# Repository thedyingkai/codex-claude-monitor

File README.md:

# Codex / Claude 配额监视器

这套项目把 Codex 和 Claude Code CLI 的配额、重置时间与活动任务数汇总到一个只读 HTTPS API，并由 Keyes E32R28T（ESP32-32E + 2.8 英寸触摸屏）便携终端显示。

推荐直接在云服务器运行 `quota-monitor standalone`。一个进程同时负责额度采集、Hooks、SQLite 和 API，本地电脑无需再运行 Agent。Codex/Claude 的登录凭据仍由官方 CLI 保存在云服务器的当前用户目录，本项目不读取或复制 OAuth Token。

> v1 只服务同一位用户的一个 Codex 账号和一个 Claude 账号。它不提供网页后台，也不显示订阅到期日期。某个账号没有 5h 或 7d 窗口时，API 返回 `null`，终端显示 `N/A`。Standalone 只能统计云服务器上运行的 Codex/Claude 任务；本地电脑上的任务不会出现在计数中。

服务器内存要按 Go 服务和官方 CLI 的总占用估算。[Codex CLI 官方要求](https://github.com/openai/codex/blob/main/docs/install.md#system-requirements)至少 4GB、推荐 8GB，[Claude Code 官方要求](https://code.claude.com/docs/en/setup#system-requirements)4GB 以上，因此官方支持配置至少应有 4GB。Standalone 默认按 Codex → 释放 app-server → Claude 的顺序串行探测，减少两个 CLI 的内存重叠，但无法降低单个 CLI 的峰值。1 核、512MB 同时启用两者仍只适合无稳定保证的实验性试跑；至少应配置 1GB swap、保持默认串行模式并持续检查 OOM，现有业务出现内存压力时应关闭一个 provider 或升级内存。

## 交付内容

- `quota-monitor standalone`：推荐模式；在云服务器单进程运行 API、SQLite、额度采集和 Hooks，本地无需 Agent。
- `quota-monitor login codex|claude`：调用官方 CLI 完成交互登录；登录失效时重新执行即可，Standalone 会自动恢复采集。
- `quota-monitor server` + `quota-monitor agent`：兼容多机上报模式，适合确实需要统计多台电脑任务的场景。
- `quota-monitor hooks install/uninstall`：合并 Codex/Claude 用户配置、保留原 Hooks 和 Claude status line，并支持精确卸载。
- `quota-monitor token create/list/revoke`：在服务器本地管理 `agent:write` 和 `display:read` 令牌。
- `quota-monitor firmware publish`：在服务器本地校验并原子发布 E32R28T OTA 固件；公网没有上传接口。
- `deploy/`：Standalone 的用户级 systemd/Caddy 示例，以及兼容模式的 Docker Compose 部署。
- `firmware/`：PlatformIO + Arduino ESP32 + LVGL 固件；默认目标为 Keyes 62520093 E32R28T，旧 FireBeetle 目标仍可回归构建。
- `hardware/`：E32R28T 当前接线/BOM，以及已明确标记为停用的旧 DFRobot 载板和外壳资料。

```text
Codex app-server / Hooks ─┐
                          ├─> quota-monitor standalone + SQLite <──HTTPS── E32R28T
Claude /usage / Hooks ────┘             （云服务器）
```

Standalone 会直接把云端采集结果写入同一进程打开的 SQLite，不需要 `agent:write` 令牌。需要多机任务统计时仍可使用 Agent 模式：额度取 `observedAt` 最新的一份，不相加；任务按 `agentId + provider + sessionId` 去重。Agent 超过 45 秒未上报后不再计入在线或任务统计，任务事件 15 分钟没有更新则失效，额度样本超过 5 分钟标记为 `stale`。

## 开始使用

需要 Go 1.23 或更高版本。Windows、Linux amd64 和 Linux arm64 的构建方法见[快速开始](docs/quickstart.md)。云服务器推荐按以下顺序部署：

1. 在普通用户下安装官方 Codex/Claude CLI 和 `quota-monitor` 单文件程序。
2. 运行 `quota-monitor login codex`；需要 Claude 时再运行 `quota-monitor login claude`。
3. 安装 Hooks，并用 `systemd --user` 常驻运行 `quota-monitor standalone`。
4. 用宿主机 Caddy 把回环地址 `127.0.0.1:8787` 代理到 HTTPS 域名。
5. 把 Standalone 首次创建的 `display.token` 写入 ESP32。
6. 首次用 USB 烧录 v0.3.0；此后可从设备的临时 WPA2 配网页手动确认 OTA。

完整命令和服务文件见 [Standalone 云端部署](docs/standalone.md)。原来的 Docker server + 本地 Agent 流程仍保留在[快速开始](docs/quickstart.md)中，作为多机兼容方案。

生产环境必须使用受信任证书的 HTTPS。`allowInsecureHttp` 只用于回环地址上的本地开发；ESP32 固件不提供跳过证书校验的选项。

## 文档

- [快速开始与首次部署](docs/quickstart.md)
- [Standalone 单进程云端部署](docs/standalone.md)
- [运行维护、升级、备份与故障排查](docs/operations.md)
- [E32R28T 手机配网、熄屏与安全 OTA](docs/firmware-ota.md)
- [测试与验收清单](docs/testing.md)
- [R0.1 自动验证报告](docs/verification-report.md)
- [系统架构](docs/architecture.md)
- [安全说明](docs/security.md)
- [OpenAPI 3.1 契约](api/openapi.yaml)
- [E32R28T 购买、接线、烧录与装配](docs/hardware/README.md)

## API

公开路径固定为：

- `GET /healthz`：无需令牌，仅表示服务与数据库可用。
- `POST /api/v1/agent/report`：多机 Agent 兼容接口，需要与 `agentId` 绑定的 `agent:write` Bearer 令牌；Standalone 自身不经过此接口。
- `GET /api/v1/display/snapshot`：需要 `display:read` Bearer 令牌。
- `GET /api/v1/display/firmware/e32r28t/manifest`：需要同一只读令牌，返回当前发布版本、大小和 SHA-256。
- `GET /api/v1/display/firmware/e32r28t/{version}.bin`：需要同一只读令牌，流式下载当前发布固件。

服务不开放 CORS、管理页面、固件上传或远程令牌管理接口。设备配网页只存在于临时
WPA2 热点的 `192.168.4.1`，不会从正常 Wi-Fi 或云服务器开放。单次 Agent 上报上限为 64 KiB；
默认每个有效令牌每分钟最多 120 次请求，令牌校验前另有哈希指纹限速、全局上限
和并发上限。

## 安全与隐私

SQLite 只保存令牌 SHA-256 摘要、最新规范化额度、Agent 心跳和不透明任务 ID；不保存提示词、对话、路径、邮箱或 OAuth Token。Standalone 首次运行会创建一个只读显示令牌文件，必须像密码一样保护。多机模式的原始 Bearer 令牌只在创建时显示一次；应为每台设备单独签发，丢失设备后立即撤销。

仓库不应提交 `.env`、数据库、显示令牌、OAuth/API 凭据、Wi-Fi 配置、完整 Flash 备份、服务器私钥或现网专用 CA。`work/`、`dist/`、`.tools/` 和 `firmware/.pio/` 均为本地目录并已被 Git 忽略。编译固件前，将部署环境的公开设备根证书放到 `firmware/certs/device-root-ca.pem`；该文件只在本机使用，仓库仅提供不连接任何生产服务器的示例证书。

锂电池必须使用带保护板、极性匹配的 3.7V/1S 成品电池，禁止直接焊接软包电芯极耳。MX1.25-2P 只说明接口外形，插入 E32R28T 前仍必须按板上 `+/-` 丝印和万用表复核线序；充电温升、续航和外壳膨胀余量未经真机测量前不能视为量产验证完成。

## 许可证

[MIT](LICENSE)

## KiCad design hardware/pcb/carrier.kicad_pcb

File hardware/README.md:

# Hardware status

## Current build

Use [`e32r28t/`](e32r28t/) and [`wiring/`](wiring/). The selected Keyes
E32R28T is an integrated display/controller/charger board, so the current build
requires no custom PCB and no separate Wi-Fi module.

## Superseded files

The following directories are retained only as history from the abandoned
DFR0975 + DFR0665 carrier design:

- `pcb/`
- `rendered/pcb/`
- `enclosure/quota_display.scad` and its rendered outputs
- `scripts/` that generate or verify the old carrier

**Do not order, fabricate, assemble or print those files for E32R28T.** Their
production status is explicitly marked `SUPERSEDED — DO NOT ORDER OR FABRICATE`.
The current enclosure must be regenerated after measuring the purchased board,
battery, connector projection and required LiPo swelling clearance.

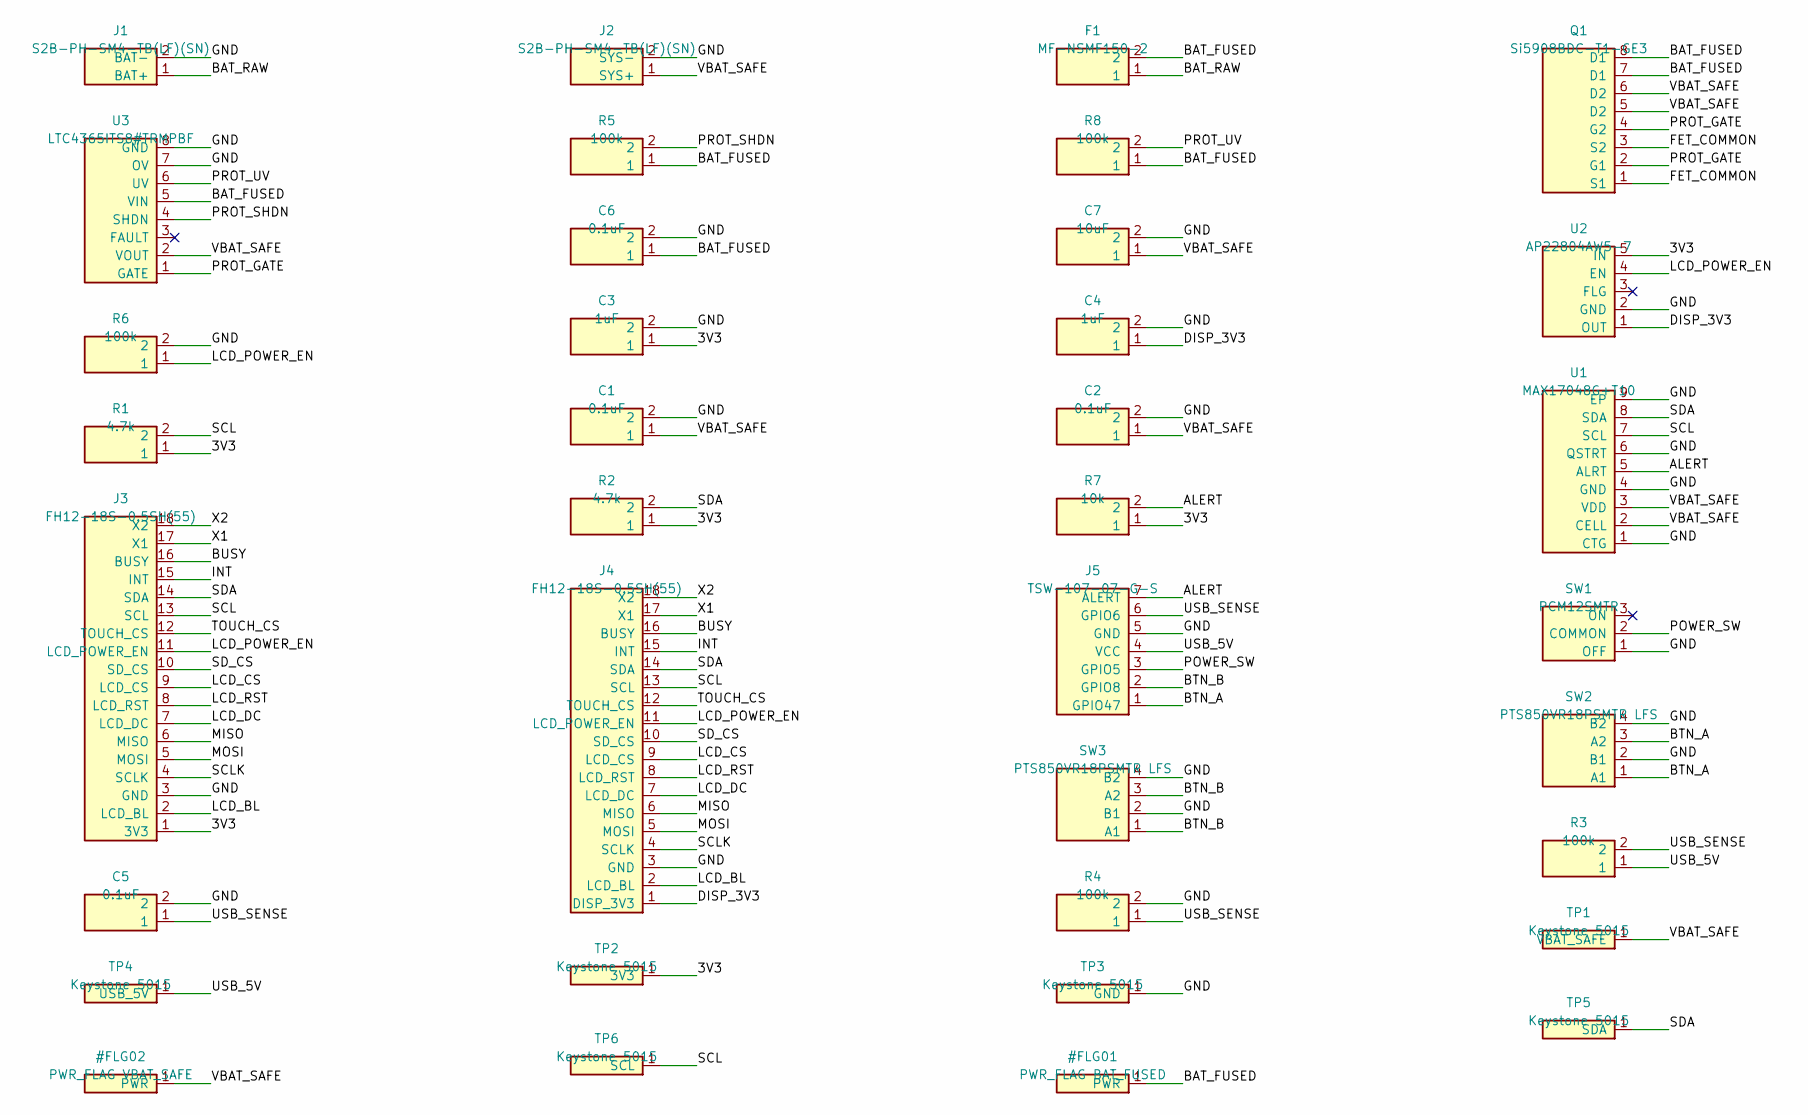
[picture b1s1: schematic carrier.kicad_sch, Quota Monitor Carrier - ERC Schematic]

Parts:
C1, C2, C5, C6: 0.1uF; C_0603
C3, C4: 1uF; C_0603
C7: 10uF; Murata_GRM21_Reflow_a1.10_b0.95_c0.95
F1: MF-NSMF150-2; Bourns_MF-NSMF_1206
J1, J2: S2B-PH-SM4-TB(LF)(SN); JST_PH_S2B-PH-SM4-TB_1x02_P2.00mm_Horizontal
J3, J4: FH12-18S-0.5SH(55); Hirose_FH12-18S-0.5SH_1x18_P0.50mm
J5: TSW-107-07-G-S; PinHeader_1x07_P2.54mm
Q1: Si5908BDC-T1-GE3; Vishay_1206-8_ChipFET
R1, R2: 4.7k; R_0603
R3, R4, R5, R6, R8: 100k; R_0603
R7: 10k; R_0603
SW1: PCM12SMTR; C&K_PCM12SMTR
SW2, SW3: PTS850VR18PSMTR LFS; C&K_PTS850_with_boss_actuator_plusX
TP1, TP2, TP3, TP4, TP5, TP6: Keystone 5015; Keystone_5015_SMT
U1: MAX17048G+T10; ADI_TDFN-8-1EP_2x2_P0.5_EP0.8x1.2
U2: AP22804AW5-7; Diodes_SOT-25_AP22804
U3: LTC4365ITS8#TRMPBF; TSOT-23-8

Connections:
3V3: C3.1, J3.1 (3V3), R1.1, R2.1, R7.1, TP2.1 (3V3), U2.5 (IN)
ALERT: J5.7 (ALERT), R7.2, U1.5 (ALRT)
BAT_FUSED: C6.1, F1.2, Q1.7 (D1), Q1.8 (D1), R5.1, R8.1, U3.5 (VIN)
BAT_RAW: F1.1, J1.1 (+)
BTN_A: J5.1 (GPIO47), SW2.1 (CONTACT_A), SW2.3 (CONTACT_A)
BTN_B: J5.2 (GPIO8), SW3.1 (CONTACT_A), SW3.3 (CONTACT_A)
BUSY: J3.16 (BUSY), J4.16 (BUSY)
DISP_3V3: C4.1, J4.1 (DISP_3V3), U2.1 (OUT)
FET_COMMON: Q1.1 (S1), Q1.3 (S2)
GND: C1.2, C2.2, C3.2, C4.2, C5.2, C6.2, C7.2, J1.2 (-), J2.2 (-), J3.3 (GND), J4.3 (GND), J5.5 (GND), R4.2, R6.2, SW1.1 (OFF), SW2.2 (CONTACT_B), SW2.4 (CONTACT_B), SW3.2 (CONTACT_B), SW3.4 (CONTACT_B), TP3.1 (GND), U1.1 (CTG), U1.4 (GND), U1.6 (QSTRT), U1.9 (EP), U2.2 (GND), U3.7 (OV), U3.8 (GND)
INT: J3.15 (INT), J4.15 (INT)
LCD_BL: J3.2 (LCD_BL), J4.2 (LCD_BL)
LCD_CS: J3.9 (LCD_CS), J4.9 (LCD_CS)
LCD_DC: J3.7 (LCD_DC), J4.7 (LCD_DC)
LCD_POWER_EN: J3.11 (LCD_POWER_EN), J4.11 (LCD_POWER_EN), R6.1, U2.4 (EN)
LCD_RST: J3.8 (LCD_RST), J4.8 (LCD_RST)
MISO: J3.6 (MISO), J4.6 (MISO)
MOSI: J3.5 (MOSI), J4.5 (MOSI)
POWER_SW: J5.3 (GPIO5), SW1.2 (COMMON)
PROT_GATE: Q1.2 (G1), Q1.4 (G2), U3.1 (GATE)
PROT_SHDN: R5.2, U3.4 (SHDN)
PROT_UV: R8.2, U3.6 (UV)
SCL: J3.13 (SCL), J4.13 (SCL), R1.2, TP6.1 (SCL), U1.7 (SCL)
SCLK: J3.4 (SCLK), J4.4 (SCLK)
SDA: J3.14 (SDA), J4.14 (SDA), R2.2, TP5.1 (SDA), U1.8 (SDA)
SD_CS: J3.10 (SD_CS), J4.10 (SD_CS)
TOUCH_CS: J3.12 (TOUCH_CS), J4.12 (TOUCH_CS)
USB_5V: J5.4 (VCC), R3.1, TP4.1 (USB_5V)
USB_SENSE: C5.1, J5.6 (GPIO6), R3.2, R4.1
VBAT_SAFE: C1.1, C2.1, C7.1, J2.1 (+), Q1.5 (D2), Q1.6 (D2), TP1.1 (VBAT_SAFE), U1.2 (CELL), U1.3 (VDD), U3.2 (VOUT)
X1: J3.17 (X1), J4.17 (X1)
X2: J3.18 (X2), J4.18 (X2)

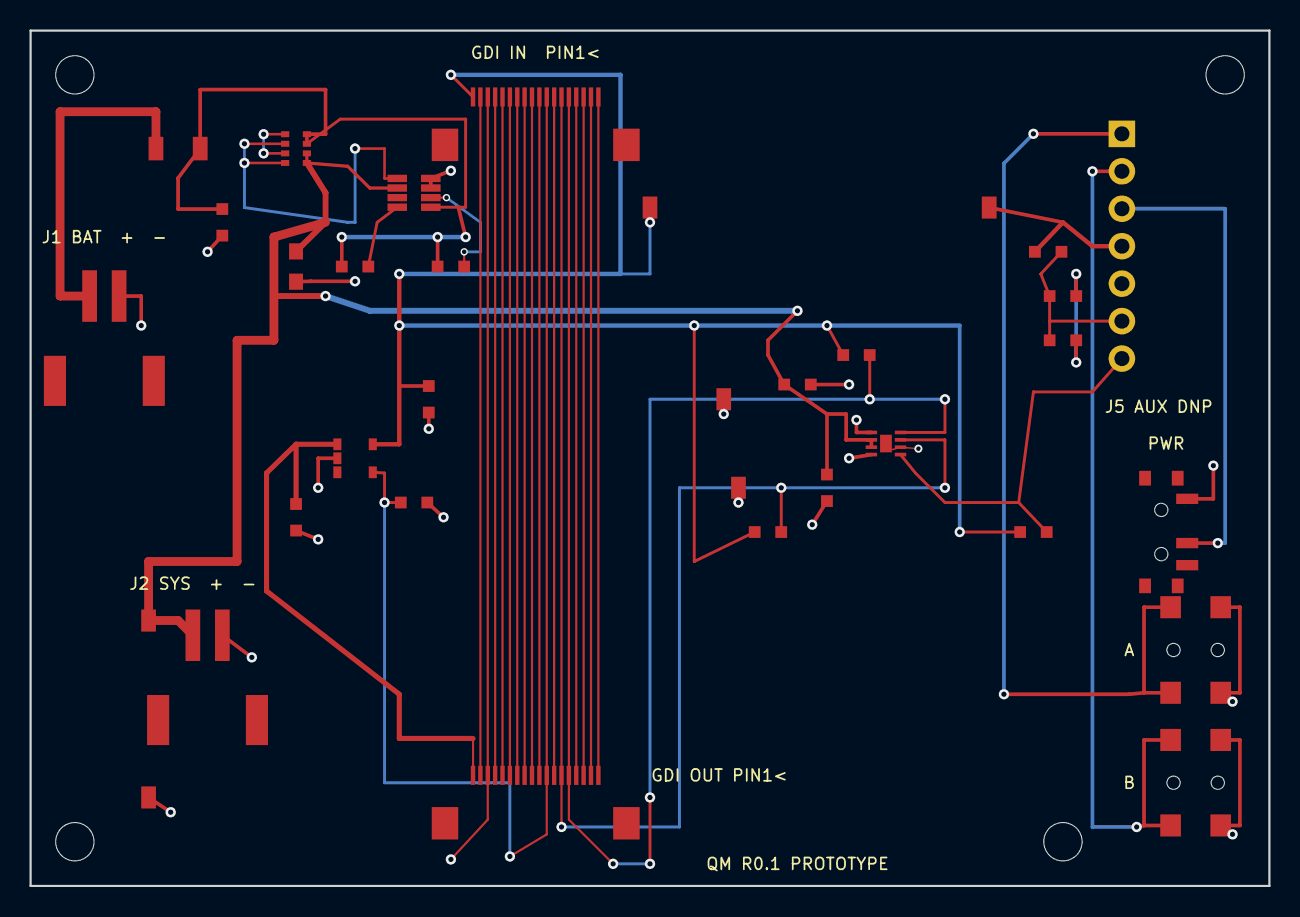
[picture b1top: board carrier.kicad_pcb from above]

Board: 2 copper layers, 84.0 x 58.0 mm, 38 parts (0 on the bottom side), 32 nets.

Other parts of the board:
H1, H2, H3, H4: M2.5_NPTH; MountingHole_2.6mm

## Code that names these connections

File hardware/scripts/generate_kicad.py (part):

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        two_pad("R2", "4.7k", 56, 22, "3V3", "SDA"),
        two_pad("R7", "10k", 68, 34, "3V3", "ALERT"),
        footprint("J5", "TSW-107-07-G-S", 74, 7,
                  [th(1, 0, 0, "BTN_A", "GPIO47", drill=1.02),
                   th(2, 0, 2.54, "BTN_B", "GPIO8", drill=1.02),
                   th(3, 0, 5.08, "POWER_SW", "GPIO5", drill=1.02),
                   th(4, 0, 7.62, "USB_5V", "VCC", drill=1.02),
                   th(5, 0, 10.16, "GND", "GND", drill=1.02),
                   th(6, 0, 12.70, "USB_SENSE", "GPIO6", drill=1.02),
                   th(7, 0, 15.24, "ALERT", "ALERT", drill=1.02)],
                  4, 18.8, "PinHeader_1x07_P2.54mm"),
        pts850("SW2", "PTS850VR18PSMTR LFS", 79, 42, "BTN_A"),
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        component("J4", "FH12-18S-0.5SH(55)",
                  ["DISP_3V3"] + gdi[1:], ["DISP_3V3"] + gdi[1:]),
        component("J5", "TSW-107-07-G-S",
                  ["GPIO47", "GPIO8", "GPIO5", "VCC", "GND", "GPIO6", "ALERT"],
                  ["BTN_A", "BTN_B", "POWER_SW", "USB_5V", "GND",
                   "USB_SENSE", "ALERT"]),
        component("SW1", "PCM12SMTR", ["OFF", "COMMON", "ON"],
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
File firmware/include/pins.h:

#pragma once

// Board capabilities are compile-time constants so GPIOs from one target are
// never even referenced by the other target. This matters on the classic ESP32:
// GPIO6..11 belong to its flash interface and must not inherit the old carrier's
// GPIO6/GPIO7 USB-sense/load-switch assignments.
#if defined(QUOTA_BOARD_E32R28T)

#define QUOTA_HAS_MAX17048 0
#define QUOTA_HAS_CARRIER_POWER 0
#define QUOTA_HAS_EXTERNAL_POWER_SENSE 1
#define QUOTA_HAS_SECOND_BUTTON 0
#define QUOTA_HAS_TOUCH 1

// Keyes 62520093 E32R28T (ESP32-WROOM-32E + ILI9341 + XPT2046).
constexpr int PIN_LCD_MISO = 12;
constexpr int PIN_LCD_MOSI = 13;
constexpr int PIN_LCD_SCLK = 14;
constexpr int PIN_LCD_CS = 15;
constexpr int PIN_LCD_DC = 2;
constexpr int PIN_LCD_RST = -1;  // LCD reset is tied to ESP32 EN.
constexpr int PIN_LCD_BACKLIGHT = 21;

constexpr int PIN_TOUCH_SCLK = 25;
constexpr int PIN_TOUCH_MOSI = 32;
constexpr int PIN_TOUCH_MISO = 39;
constexpr int PIN_TOUCH_CS = 33;
constexpr int PIN_TOUCH_IRQ = 36;  // Active low; input-only GPIO.
constexpr int PIN_BATTERY_ADC = 34;
// Optional USB +5 V detector input. GPIO35 must only be enabled after the
// documented 100k/150k divider and external pulldown are installed.
constexpr int PIN_EXTERNAL_POWER_SENSE = 35;

constexpr int PIN_SD_CS = 5;
constexpr int PIN_EXTERNAL_SPI_CS = 27;
constexpr int PIN_AUDIO_ENABLE = 4;  // Active low; keep high when unused.
constexpr int PIN_RGB_RED = 22;      // Common-anode RGB LED, active low.
constexpr int PIN_RGB_GREEN = 16;
constexpr int PIN_RGB_BLUE = 17;
constexpr int PIN_BUTTON_A = 0;  // BOOT button; only use after firmware boot.

#elif defined(QUOTA_BOARD_FIREBEETLE2)

#define QUOTA_HAS_MAX17048 1
#define QUOTA_HAS_CARRIER_POWER 1
#define QUOTA_HAS_EXTERNAL_POWER_SENSE 0
#define QUOTA_HAS_SECOND_BUTTON 1
#define QUOTA_HAS_TOUCH 0

// Legacy DFRobot FireBeetle 2 ESP32-S3 (DFR0975) GDI mapping.
// DFR0665 touch and micro-SD are intentionally unused on this target.
constexpr int PIN_LCD_MISO = 16;
constexpr int PIN_LCD_MOSI = 15;
constexpr int PIN_LCD_SCLK = 17;
constexpr int PIN_LCD_CS = 18;
constexpr int PIN_LCD_DC = 3;
constexpr int PIN_LCD_RST = 38;
constexpr int PIN_LCD_BACKLIGHT = 21;
constexpr int PIN_SD_CS = 9;      // DFR0665 microSD is unused; hold deselected.
constexpr int PIN_TOUCH_CS = 12;  // DFR0665 XPT2046 is unused; hold deselected.

constexpr int PIN_I2C_SDA = 1;
constexpr int PIN_I2C_SCL = 2;
constexpr int PIN_BUTTON_A = 47;       // FireBeetle onboard/user button line.
constexpr int PIN_BUTTON_B = 8;        // Carrier tactile switch to GND.
constexpr int PIN_POWER_SWITCH = 5;    // ON=open/high, OFF=closed to GND.
constexpr int PIN_USB_SENSE = 6;       // 100k/100k divider from USB/VCC 5 V.
constexpr int PIN_DISPLAY_ENABLE = 7;  // AP22804 load-switch EN.

constexpr uint8_t MAX17048_ADDRESS = 0x36;

#else
#error "Select exactly one supported quota-monitor board profile"
#endif
